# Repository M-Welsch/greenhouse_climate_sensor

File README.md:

# greenhouse_climate_sensor
small climate sensor unit with LiPO battery and an ESP8266

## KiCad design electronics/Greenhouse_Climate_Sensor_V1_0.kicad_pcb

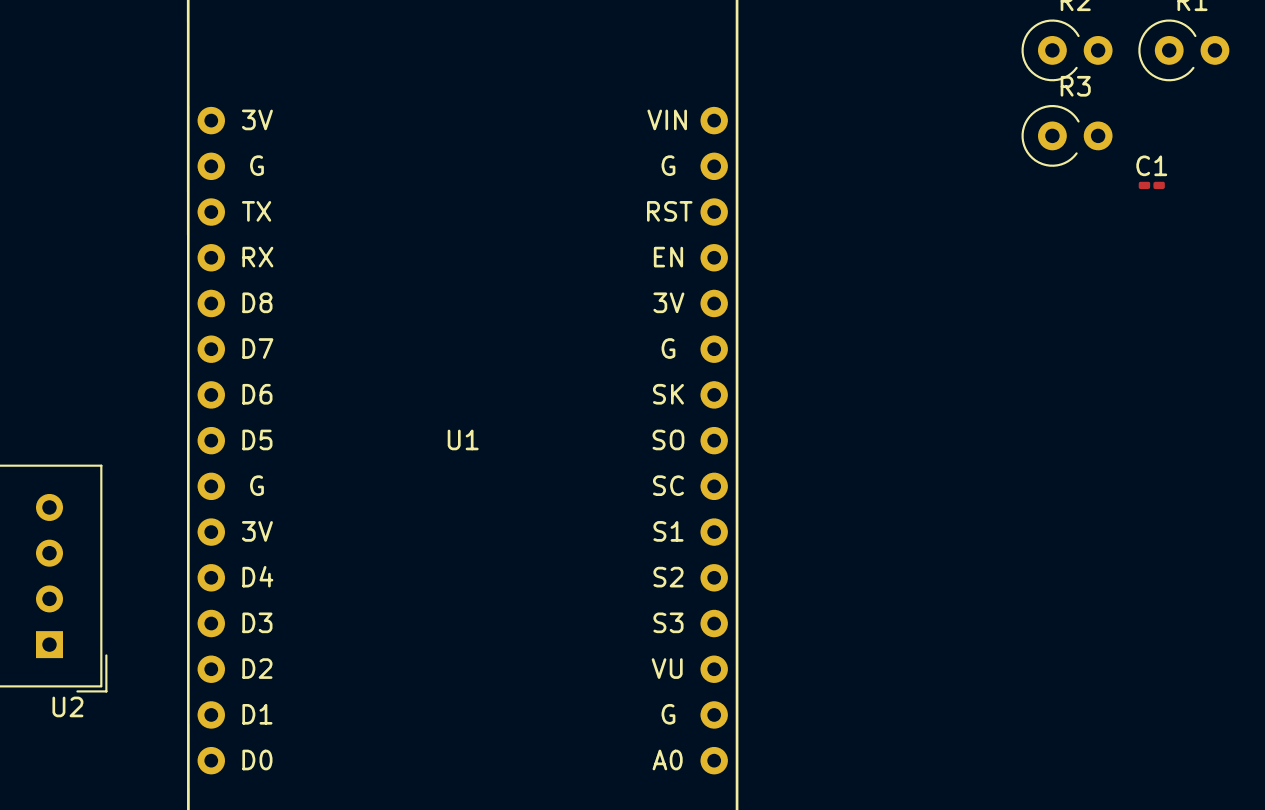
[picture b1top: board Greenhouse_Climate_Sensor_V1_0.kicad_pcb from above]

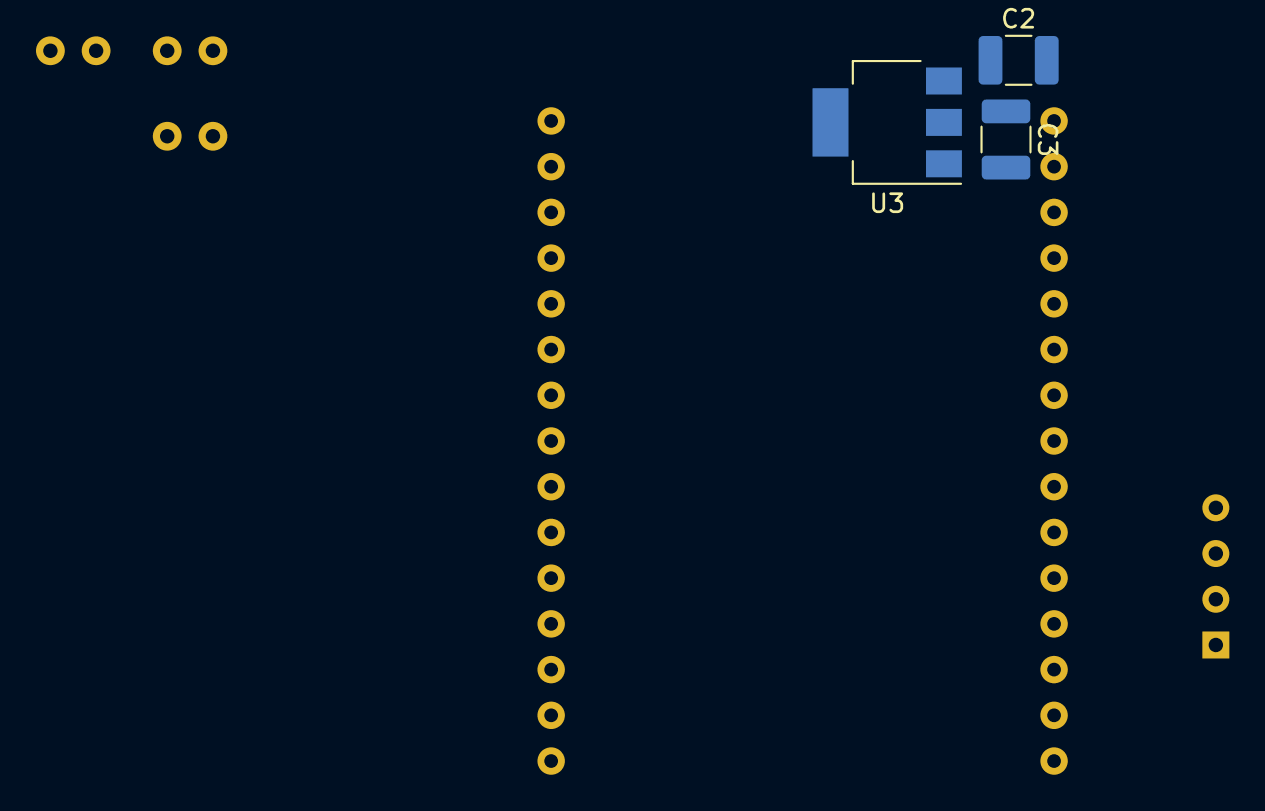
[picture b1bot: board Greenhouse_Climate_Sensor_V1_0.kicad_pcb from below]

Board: 2 copper layers, 9 parts (3 on the bottom side), 5 nets, no tracks yet.

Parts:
C1: 100nF; C_0201_0603Metric_Pad0.64x0.40mm_HandSolder
C2, C3: 22µF; C_1210_3225Metric_Pad1.33x2.70mm_HandSolder
R1: 56k; R_Axial_DIN0309_L9.0mm_D3.2mm_P2.54mm_Vertical
R2: 150k; R_Axial_DIN0309_L9.0mm_D3.2mm_P2.54mm_Vertical
R3: 10k; R_Axial_DIN0309_L9.0mm_D3.2mm_P2.54mm_Vertical
U1: NodeMCU_1.0_(ESP-12E); NodeMCU1.0(12-E)
U2: DHT22; Aosong_DHT11_5.5x12.0_P2.54mm
U3: AMS1117-3.3; SOT-223-3_TabPin2

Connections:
+3.3V: C3.1, R3.1, U1.11 (3.3V), U1.16 (3.3V), U1.25 (3.3V), U2.1 (VCC), U3.2 (VO)
+BATT: C2.1, R1.1, U3.3 (VI)
/dht_data: R3.2, U1.27 (D3(GPIO0)), U2.2 (IO)
/vbat_div: C1.1, R1.2, R2.1, U1.1 (A0(ADC0))
GND: C1.2, C2.2, C3.2, R2.2, U1.10 (GND), U1.14 (GND), U1.17 (GND), U1.24 (GND), U2.4 (GND), U3.1 (GND)

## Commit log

2022-11-24 sketch out schematic
2022-11-25 add minimally functional firmware. Probably final changes to hardware
2022-11-25 goes to sleep for 60s after each measurement. Doesn't do anything if battery is low, checks after 1h.
2022-11-27 add stub for storing old values in flash. Calibrated ADC
2022-12-01 main.cpp: open hotspot if button is pressed during startup
2022-12-01 mqtt.cpp: has maximum number of trials
2022-12-17 reconfigure for mobile climate sensor
